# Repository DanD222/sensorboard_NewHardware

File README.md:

# sensorboard_NewHardware
Hardware for a new version of the OpenVario Sensorboard, stemming from discussion in these issues:

https://github.com/Openvario/sensord/issues/23

https://github.com/Openvario/sensord/issues/26

Features / comparison to the original OpenVario sensorboard:

   - Added an ESP32 for polling the sensors and connectivity to the outside world
   - Updated sensors and voltage regulators
   - A USB connector has been added in place of the 6pin I2C connector
   - There are footprints for three differential sensors (DLHR-L30G-E1BD-C-NAV8, 4515DO-DS3BK030DPL, AMS5915)
   - There are two I2C buses:
       - 1 - SDA0/SCL0 is the on-board sensor I2C bus, this goes to the ESP32
       - 2 - SDA1/SCL0 is the external I2C bus, going from the ESP32 to the 10pin IDC connector
       
     Both buses can be linked via solder jumpers on the bottom layer - this allows the sensors to be connected to the IDC connector directly without using the ESP32. This can be useful to get the new sensorboard integrated into the current OpenVario setup without having to implement the ESP32 first.
   - Pins for UART0 and UART1. The UART0 pin header has a 5V pin, so that it can connect for example directly to a HC-05 Bluetooth module (or a board with an RS232 interface)
   - An on-board 12V->5V PSU so that the sensorboard can be used stand-alone
   - Additional filtering - 5VD powers the digital stuff (USB, ESP32 voltage regulator); 5VC powers the sensitive stuff (sensor voltage regulators, audio amp)
   - The audio amp is a class AB TPA6211A1DRBR
   - There are pins around the audio amp so that a daughter board can be used in order to experiment with different amps
   - There are pins for selecting the source to the audio amp. This can be either the ESP32 for future use, or external input (to be backwards-compatible)
   - The OAT sensor has been moved to a 2.5mm jack
   - The audio output is on a 3.5mm stereo jack

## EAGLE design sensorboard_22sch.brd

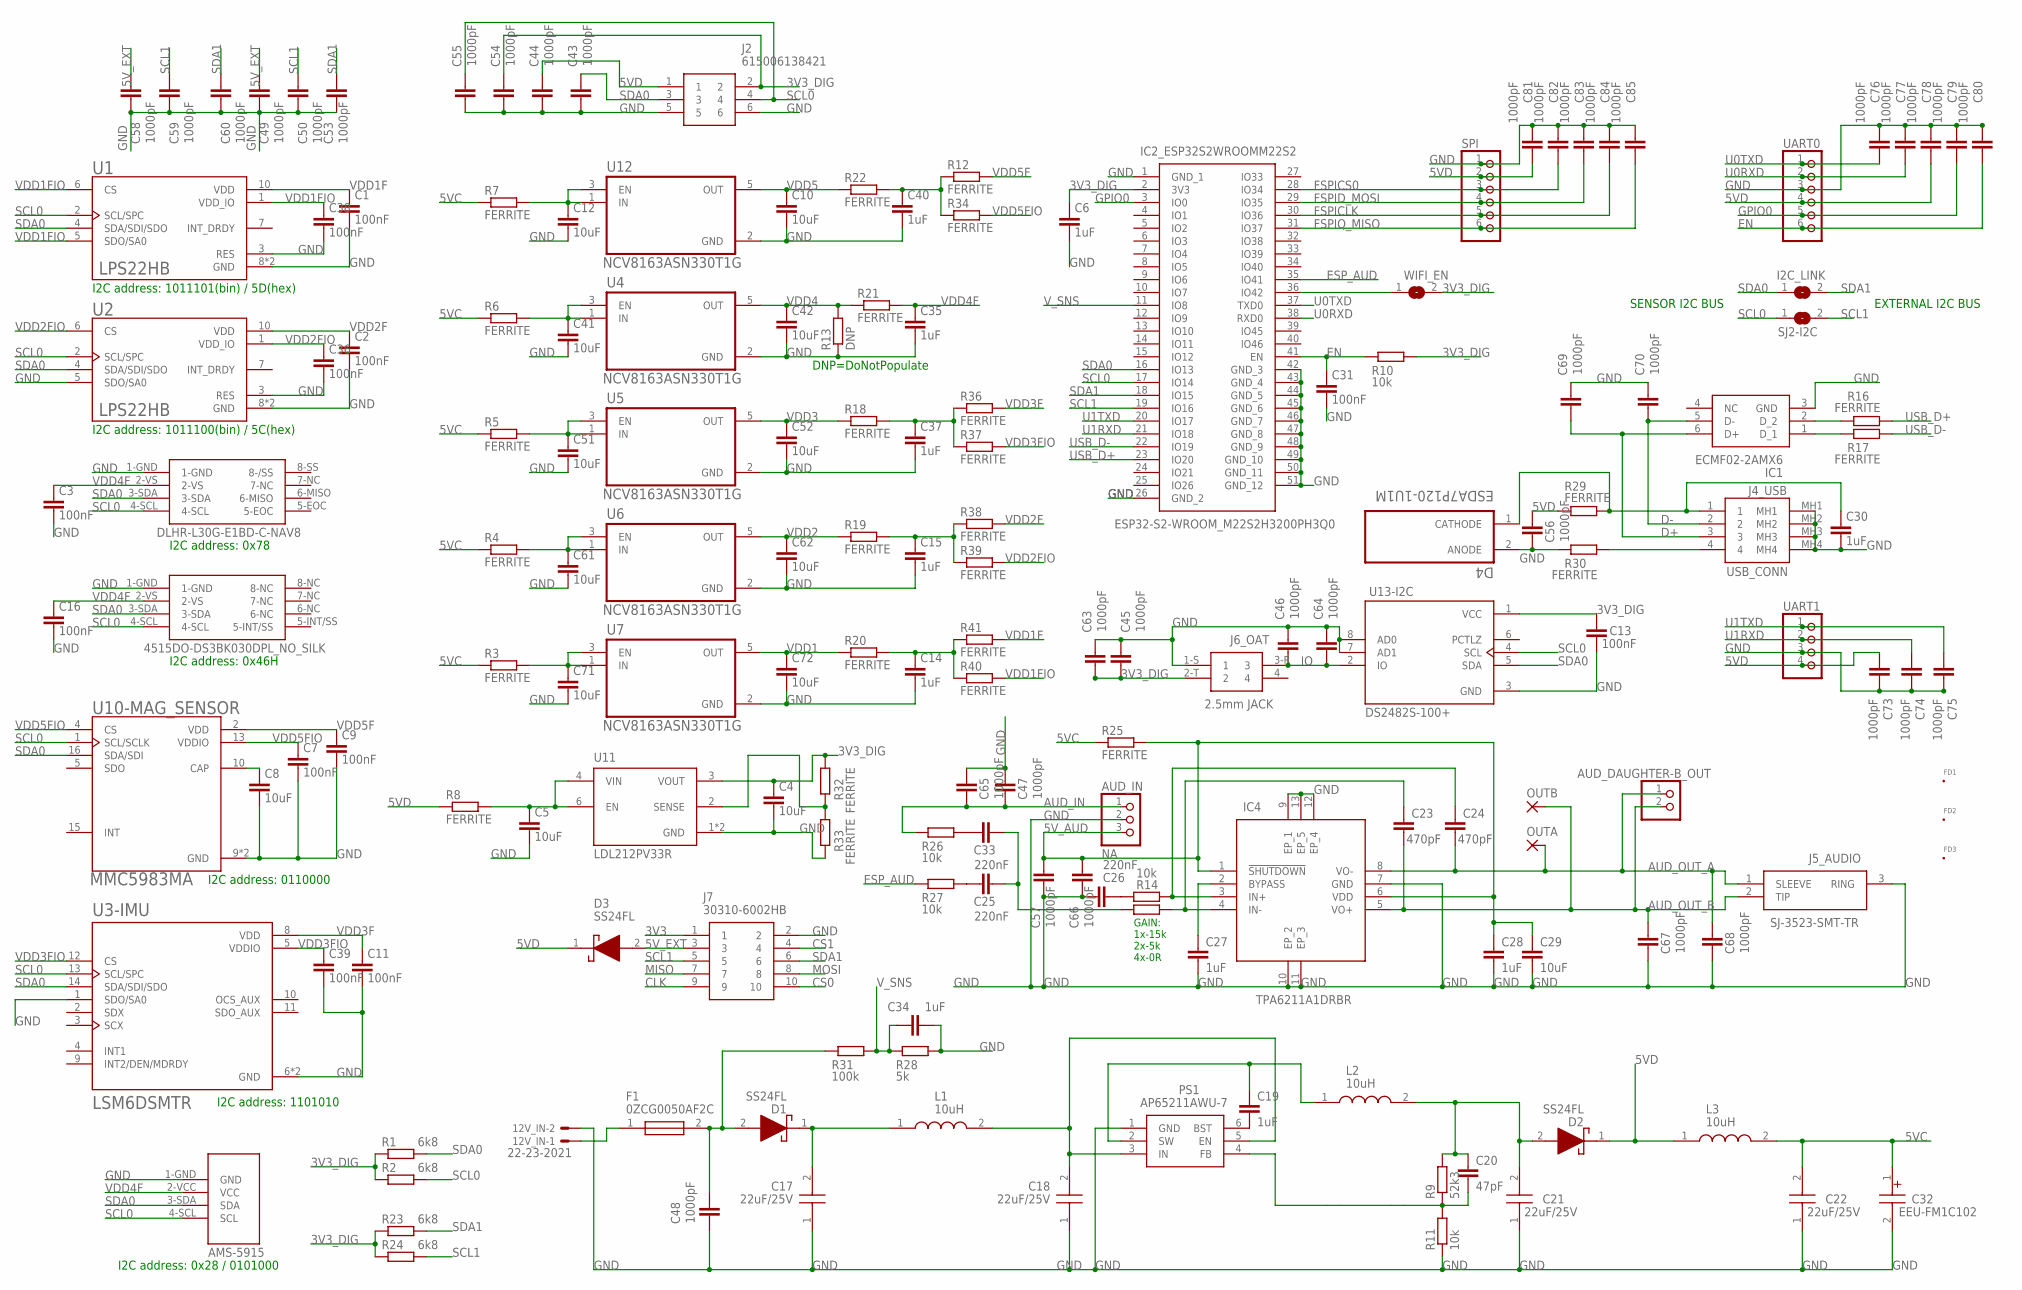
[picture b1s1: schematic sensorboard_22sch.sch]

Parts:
12V_IN: 22-23-2021
AUD_DAUGHTER-B_OUT: PINHD-1X2; 1X02
AUD_IN: NA; 1X03
C1, C2, C3, C7, C9, C11, C13, C16, C31, C36, C38, C39: 100nF; C0402
C4, C5, C8, C10, C12, C29, C41, C42, C51, C52, C61, C62, C71, C72: 10uF; C0805
C6, C14, C15, C19, C27, C28, C30, C34, C35, C37, C40: 1uF; C0603
C17, C18, C21, C22: 22uF/25V; CAPC3216X180N
C20: 47pF; C0402
C23, C24: 470pF; C0805
C25, C26, C33: 220nF; C1206
C32: EEU-FM1C102; CAPPRD500W65D1000H2200
C43, C44, C45, C46, C47, C48, C49, C50, C53, C54, C55, C56, C57, C58, C59, C60, C63, C64, C65, C66, C67, C68, C69, C70, C73, C74, C75, C76, C77, C78, C79, C80, C81, C82, C83, C84, C85: 1000pF; C0402
D1, D2, D3: SS24FL; SODFL3617X108N
D4: ESDA7P120-1U1M; DIO_ESDA13P70-1U1M
DLHR-L30G-E1BD-C-NAV8: DLHR-L30G-E1BD-C-NAV8
F1: 0ZCG0050AF2C; FUSC4632X75N
FD1, FD2, FD3: FID_20MIL_P; FID_020_P
I2C_LINK: SJ
IC1: ECMF02-2AMX6; SON50P150X170X55-6N
IC2_ESP32S2WROOMM22S2: ESP32-S2-WROOM_M22S2H3200PH3Q0; ESP32S2WROOMM22S2H3200PH3Q0
IC4: TPA6211A1DRBR; TPS7A8033DRBT
J2: 615006138421
J4_USB: USB_CONN; 737250110BLF
J5_AUDIO: SJ-3523-SMT-TR; SJ3523SMTTR
J6_OAT: 2.5mm JACK; SJ-2523-SMT-TR
J7: 30310-6002HB; SHDR10W64P254_2X5_2030X878X930
L1, L2, L3: 10uH; FDSD0420WH150MP3
OUTA: SMD2_SMALLSMALL; SMD2_SMALL
OUTB: SMD2_SMALLSMALL; SMD2_SMALL
PS1: AP65211AWU-7; SOT95P280X90-6N
R1, R2, R23, R24: 6k8; R0402
R3, R4, R5, R6, R7, R8, R12, R16, R17, R18, R19, R20, R21, R22, R25, R29, R30, R34, R36, R37, R38, R39, R40, R41: FERRITE; R0805
R9: 52k3; R0402
R10, R11, R14, R26, R27: 10k; R0402
R13: DNP; R0805
R15: R-EU_R0402; R0402
R28: 5k; R0402
R31: 100k; R0402
R32, R33: FERRITE; R0402
SJ2-I2C: SJ
SPI: PINHD-1X6; 1X06
U1, U2: LPS22HB; LGA10R50P2X3_200X200X80
U3-IMU: LSM6DSMTR; PQFN50P300X250X86-14N
U4, U5, U6, U7, U12: NCV8163ASN330T1G; SOP95P275X110-5N
U10-MAG_SENSOR: MMC5983MA; LGA16R50P4X4_330X330X100
U11: LDL212PV33R; SON50P200X200X80-7N
U13-I2C: DS2482S-100+; SOIC127P600X175-8N
U$1: AMS-5915
U$4: 4515DO-DS3BK030DPL_NO_SILKNO_SILK; 4515DO-DS3BK030DPL_NO_SILK
UART0: PINHD-1X6; 1X06
UART1: PINHD-1X4; 1X04
WIFI_EN: SJ

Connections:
3V3: J7.1
3V3_DIG: C4.1, C6.1, C13.1, C45.1, C54.2, C63.1, IC2_ESP32S2WROOMM22S2.2 (3V3), J2.2, J6_OAT.2-T (2), R1.1, R2.1, R10.2, R23.1, R24.1, R32.2, U11.3 (VOUT), U13-I2C.1 (VCC), WIFI_EN.2
5VC: C22.2, C32.1 (+), L3.2, R3.1, R4.1, R5.1, R6.1, R7.1, R25.1
5VD: C44.2, C56.2, C73.1, C78.2, C81.2, D2.1 (K), D3.1 (K), J2.1, L3.1, R8.1, R29.1, SPI.2, UART0.4, UART1.4
5V_AUD: AUD_IN.3, C28.1, C29.1, C57.2, C66.2, IC4.1 (!SHUTDOWN), IC4.6 (VDD), R25.2
5V_EXT: C49.2, C58.2, D3.2 (A), J7.3
AUD_IN: AUD_IN.1, C47.1, C65.1, R26.1
AUD_OUT_A: AUD_DAUGHTER-B_OUT.1, C24.2, C68.2, IC4.8 (VO-), J5_AUDIO.1 (SLEEVE), OUTA.1
AUD_OUT_B: AUD_DAUGHTER-B_OUT.2, C23.2, C67.2, IC4.5 (VO+), J5_AUDIO.2 (TIP), OUTB.1
CLK: J7.9
CS0: J7.10
CS1: J7.4
D+: C69.1, IC1.6 (D+), J4_USB.3
D-: C70.1, IC1.5 (D-), J4_USB.2
EN: C31.1, C80.2, IC2_ESP32S2WROOMM22S2.41 (EN), R10.1, UART0.6
ESP_AUD: IC2_ESP32S2WROOMM22S2.35 (IO41), R27.1
FSPICLK: C84.2, IC2_ESP32S2WROOMM22S2.30 (IO36), SPI.5
FSPICS0: C82.2, IC2_ESP32S2WROOMM22S2.28 (IO34), SPI.3
FSPID_MOSI: C83.2, IC2_ESP32S2WROOMM22S2.29 (IO35), SPI.4
FSPIQ_MISO: C85.2, IC2_ESP32S2WROOMM22S2.31 (IO37), SPI.6
GND: 12V_IN.2, AUD_IN.2, C1.2, C2.2, C3.2, C4.2, C5.2, C6.2, C7.2, C8.2, C9.2, C10.2, C11.2, C12.2, C13.2, C14.2, C15.2, C16.2, C17.1, C18.1, C21.1, C22.1, C26.1, C27.2, C28.2, C29.2, C30.2, C31.2, C32.2 (-), C34.2, C35.2, C36.2, C37.2, C38.2, C39.2, C40.2, C41.2, C42.2, C43.1, C44.1, C45.2, C46.2, C47.2, C48.1, C49.1, C50.1, C51.2, C52.2, C53.1, C54.1, C55.1, C56.1, C57.1, C58.1, C59.1, C60.1, C61.2, C62.2, C63.2, C64.2, C65.2, C66.1, C67.1, C68.1, C69.2, C70.2, C71.2, C72.2, C73.2, C74.2, C75.2, C76.1, C77.1, C78.1, C79.1, C80.1, C81.1, C82.1, C83.1, C84.1, C85.1, D4.2 (ANODE), DLHR-L30G-E1BD-C-NAV8.1-GND, IC1.3 (GND), IC2_ESP32S2WROOMM22S2.1 (GND_1), IC2_ESP32S2WROOMM22S2.26 (GND_2), IC2_ESP32S2WROOMM22S2.42 (GND_3), IC2_ESP32S2WROOMM22S2.43 (GND_4), IC2_ESP32S2WROOMM22S2.44 (GND_5), IC2_ESP32S2WROOMM22S2.45 (GND_6), IC2_ESP32S2WROOMM22S2.46 (GND_7), IC2_ESP32S2WROOMM22S2.47 (GND_8), IC2_ESP32S2WROOMM22S2.48 (GND_9), IC2_ESP32S2WROOMM22S2.49 (GND_10), IC2_ESP32S2WROOMM22S2.50 (GND_11), IC2_ESP32S2WROOMM22S2.51 (GND_12), IC4.7 (GND), IC4.9 (EP_1), IC4.10 (EP_2), IC4.11 (EP_3), IC4.12 (EP_4), IC4.13 (EP_5), J2.5, J2.6, J4_USB.MH1, J4_USB.MH2, J4_USB.MH3, J4_USB.MH4, J5_AUDIO.3 (RING), J6_OAT.1-S (1), J7.2, PS1.1 (GND), R11.1, R13.1, R28.2, R30.1, R33.1, SPI.1, U1.3 (RES), U1.8 (GND), U1.9 (GND), U2.3 (RES), U2.5 (SDO/SA0), U2.8 (GND), U2.9 (GND), U3-IMU.1 (SDO/SA0), U3-IMU.6 (GND), U3-IMU.7 (GND), U4.2 (GND), U5.2 (GND), U6.2 (GND), U7.2 (GND), U10-MAG_SENSOR.9 (GND), U10-MAG_SENSOR.11 (GND), U11.1 (GND), U11.7 (GND), U12.2 (GND), U13-I2C.3 (GND), U13-I2C.7 (AD1), U13-I2C.8 (AD0), U$1.1-GND (GND), U$4.1-GND, UART0.3, UART1.3
GPIO0: C79.2, IC2_ESP32S2WROOMM22S2.3 (IO0), UART0.5
IO: C46.1, C64.1, J6_OAT.3-R (3), U13-I2C.2 (IO)
MISO: J7.7
MOSI: J7.8
unnamed: C8.1, U10-MAG_SENSOR.10 (CAP)
unnamed: C30.1, D4.1 (CATHODE), J4_USB.1, R29.2
unnamed: C23.1, IC4.4 (IN-), R15.2
unnamed: C17.2, D1.1 (K), L1.1
unnamed: C18.2, L1.2, PS1.3 (IN), PS1.5 (EN)
unnamed: C25.2, C33.2, R15.1
unnamed: C20.2, PS1.4 (FB), R9.1, R11.2
unnamed: C19.1, L2.1, PS1.2 (SW)
unnamed: C19.2, PS1.6 (BST)
unnamed: C24.1, IC4.3 (IN+), R14.2
unnamed: C26.2, R14.1
unnamed: J4_USB.4, R30.2
unnamed: 12V_IN.1, F1.1
unnamed: IC2_ESP32S2WROOMM22S2.36 (IO42), WIFI_EN.1
unnamed: C27.1, IC4.2 (BYPASS)
unnamed: IC1.1 (D_1), R17.1
unnamed: IC1.2 (D_2), R16.1
unnamed: C25.1, R27.2
unnamed: C33.1, R26.2
unnamed: C20.1, C21.2, D2.2 (A), L2.2, R9.2
unnamed: C48.2, D1.2 (A), F1.2, R31.1
unnamed: R32.1, R33.2, U11.2 (SENSE)
SCL0: C55.2, DLHR-L30G-E1BD-C-NAV8.4-SCL, IC2_ESP32S2WROOMM22S2.17 (IO14), J2.4, R2.2, SJ2-I2C.1, U1.2 (SCL/SPC), U2.2 (SCL/SPC), U3-IMU.13 (SCL/SPC), U10-MAG_SENSOR.1 (SCL/SCLK), U13-I2C.4 (SCL), U$1.4-SCL (SCL), U$4.4-SCL
SCL1: C50.2, C59.2, IC2_ESP32S2WROOMM22S2.19 (IO16), J7.5, R24.2, SJ2-I2C.2
SDA0: C43.2, DLHR-L30G-E1BD-C-NAV8.3-SDA, I2C_LINK.1, IC2_ESP32S2WROOMM22S2.16 (IO13), J2.3, R1.2, U1.4 (SDA/SDI/SDO), U2.4 (SDA/SDI/SDO), U3-IMU.14 (SDA/SDI/SDO), U10-MAG_SENSOR.16 (SDA/SDI), U13-I2C.5 (SDA), U$1.3-SDA (SDA), U$4.3-SDA
SDA1: C53.2, C60.2, I2C_LINK.2, IC2_ESP32S2WROOMM22S2.18 (IO15), J7.6, R23.2
U0RXD: C77.2, IC2_ESP32S2WROOMM22S2.38 (RXD0), UART0.2
U0TXD: C76.2, IC2_ESP32S2WROOMM22S2.37 (TXD0), UART0.1
U1RXD: C74.1, IC2_ESP32S2WROOMM22S2.21 (IO18), UART1.2
U1TXD: C75.1, IC2_ESP32S2WROOMM22S2.20 (IO17), UART1.1
USB_D+: IC2_ESP32S2WROOMM22S2.23 (IO20), R16.2
USB_D-: IC2_ESP32S2WROOMM22S2.22 (IO19), R17.2
VDD1: C72.1, R20.1, U7.5 (OUT)
VDD1F: C1.1, R41.2, U1.10 (VDD)
VDD1FI: C14.1, R20.2, R40.1, R41.1
VDD1FIO: C38.1, R40.2, U1.1 (VDD_IO), U1.5 (SDO/SA0), U1.6 (CS)
VDD1P: C71.1, R3.2, U7.1 (IN), U7.3 (EN)
VDD2: C62.1, R19.1, U6.5 (OUT)
VDD2F: C2.1, R38.2, U2.10 (VDD)
VDD2FI: C15.1, R19.2, R38.1, R39.1
VDD2FIO: C36.1, R39.2, U2.1 (VDD_IO), U2.6 (CS)
VDD2P: C61.1, R4.2, U6.1 (IN), U6.3 (EN)
VDD3: C52.1, R18.1, U5.5 (OUT)
VDD3F: C11.1, R36.2, U3-IMU.8 (VDD)
VDD3FI: C37.1, R18.2, R36.1, R37.1
VDD3FIO: C39.1, R37.2, U3-IMU.5 (VDDIO), U3-IMU.12 (CS)
VDD3P: C51.1, R5.2, U5.1 (IN), U5.3 (EN)
VDD4: C42.1, R13.2, R21.1, U4.5 (OUT)
VDD4F: C3.1, C16.1, C35.1, DLHR-L30G-E1BD-C-NAV8.2-VS, R21.2, U$1.2-VCC (VCC), U$4.2-VS
VDD4P: C41.1, R6.2, U4.1 (IN), U4.3 (EN)
VDD5: C10.1, R22.1, U12.5 (OUT)
VDD5F: C9.1, R12.2, U10-MAG_SENSOR.2 (VDD)
VDD5FI: C40.1, R12.1, R22.2, R34.1
VDD5FIO: C7.1, R34.2, U10-MAG_SENSOR.4 (CS), U10-MAG_SENSOR.13 (VDDIO)
VDD5P: C12.1, R7.2, U12.1 (IN), U12.3 (EN)
VDD_DIGP: C5.1, R8.2, U11.4 (VIN), U11.6 (EN)
V_SNS: C34.1, IC2_ESP32S2WROOMM22S2.11 (IO8), R28.1, R31.2

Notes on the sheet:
SENSOR I2C BUS
EXTERNAL I2C BUS
GAIN: 1x-15k 2x-5k 4x-0R
I2C address: 1101010
I2C address: 0110000
I2C address: 1011101(bin) / 5D(hex)
I2C address: 1011100(bin) / 5C(hex)
I2C address: 0x78
I2C address: 0x46H
I2C address: 0x28 / 0101000
DNP=DoNotPopulate

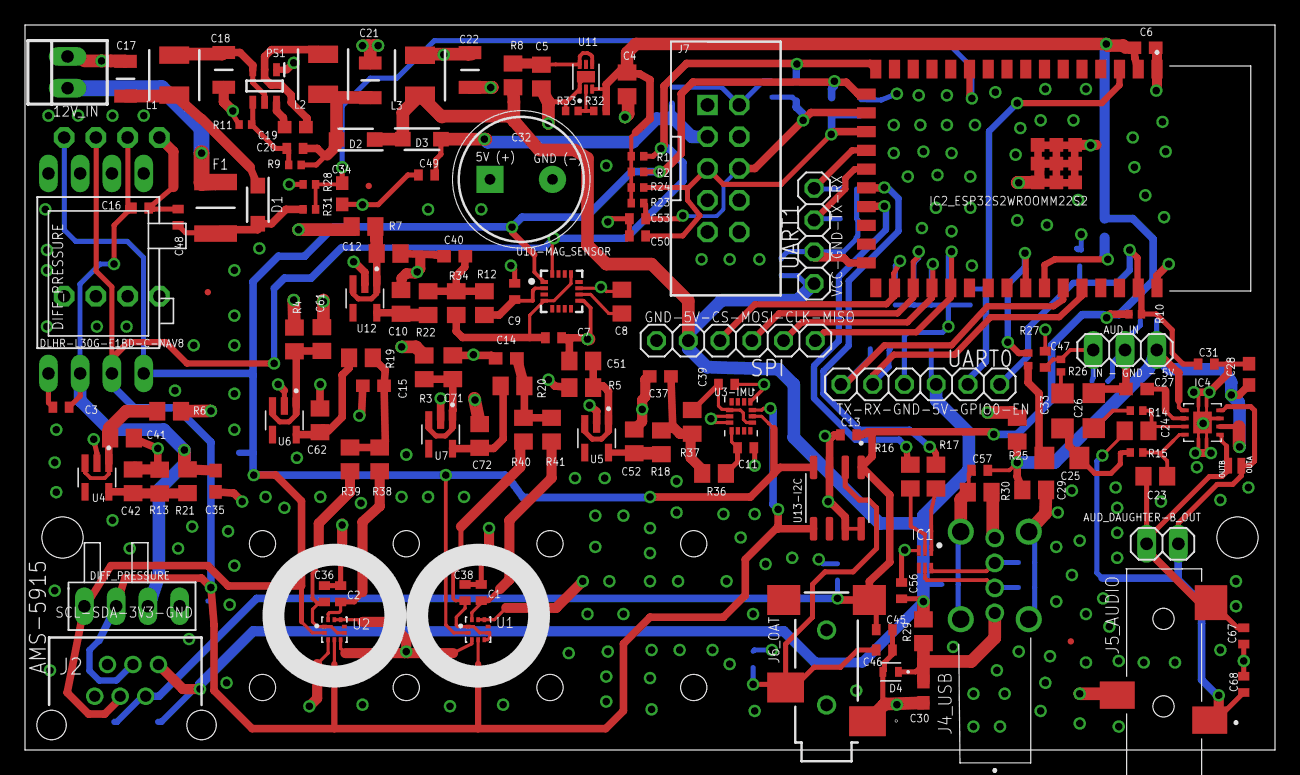
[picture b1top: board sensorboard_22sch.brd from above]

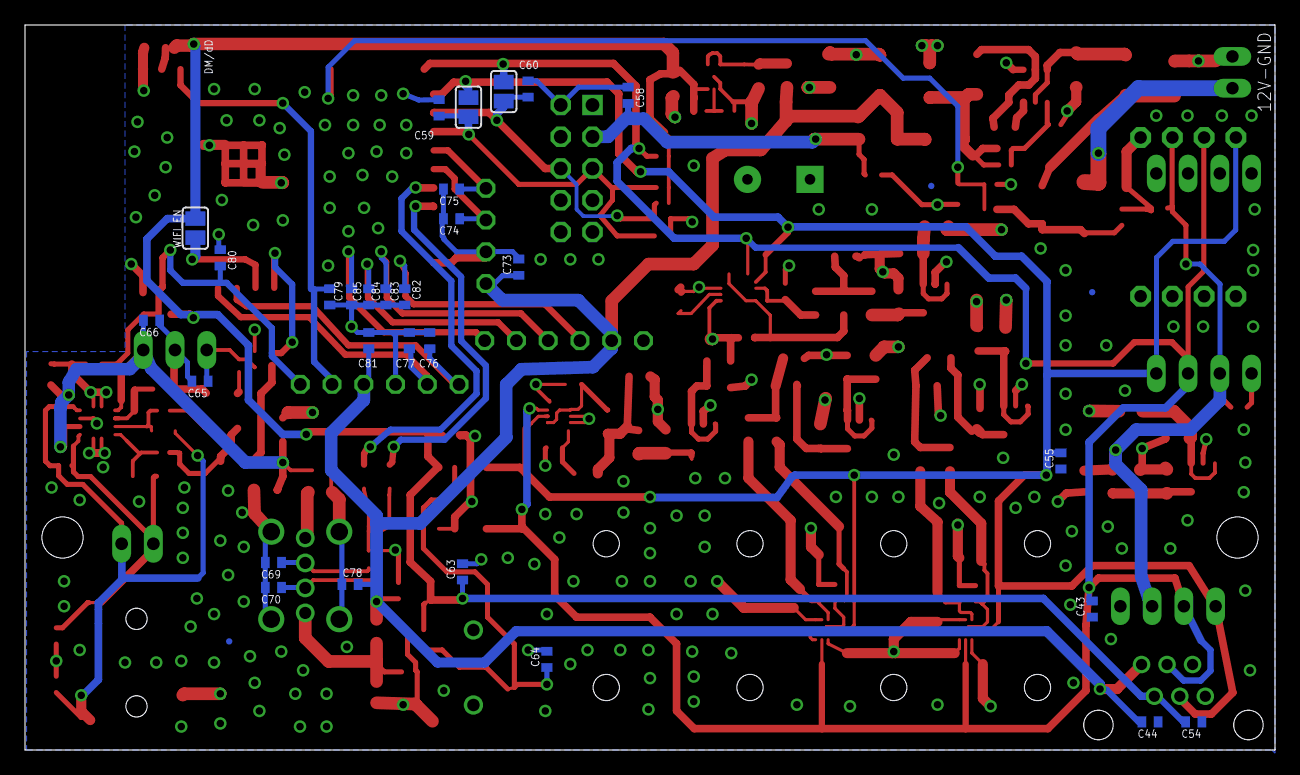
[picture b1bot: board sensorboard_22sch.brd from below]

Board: 4 copper layers, 100.0 x 58.0 mm, 170 parts (29 on the bottom side), 76 nets.

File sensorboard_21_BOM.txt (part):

Partlist exported from /Users/dan/openvario/hpmax/sensorboard_21.sch at 8/3/21 23:23 PM

Part                  Value                          Device                            Package                        Description                                                                                                                                           4515DO-DS3BK030DPL_NO_SILK AMS-5915 ARROW_ELECTRONICS-PURCHASE-URL                              AVAILABILITY DESCRIPTION                                                                                                                   DIGIKEY-PURCHASE-URL                              DLHR-L30G-E1BD-C-NAV8 HEIGHT  MANUFACTURER_NAME         MANUFACTURER_PART_NUMBER        MF                 MOUSER-PURCHASE-URL                              MOUSER_PART_NUMBER   MOUSER_PRICE-STOCK                                                                                                             MP               MPN        OC_FARNELL OC_NEWARK PACKAGE                     POPULARITY PRICE PURCHASE-URL                                                  SPICEPREFIX
12V_IN                22-23-2021                     22-23-2021                        22-23-2021                     .100" (2.54mm) Center Header - 2 Pin                                                                                                                                                                                                                                                                                                                                                                                                                                                                                                       MOLEX                                                                                                                                                                                                                                    22-23-2021 1462926    25C3832                               40                                                                                        
AUD_DAUGHTER-B_OUT                                   PINHD-1X2                         1X02                           PIN HEADER                                                                                                                                                                                                                                                                                                                                                                                                                                                                                                                                                                                                                                                                                                                                                                                                                                      98                                                                                        
AUD_IN                                               PINHD-1X3                         1X03                           PIN HEADER                                                                                                                                                                                                                                                                                                                                                                                                                                                                                                                                                                                                                                                                                                                                                                                                                                      92                                                                                        
C1                    100nF                          C-EUC0603                         C0603                          CAPACITOR, European symbol                                                                                                                                                                                                                                                                                                                                                                                                                                                                                                                                                                                                                                                                                                                                                                                                                      73                                                                             C          
C2                    100nF                          C-EUC0603                         C0603                          CAPACITOR, European symbol                                                                                                                                                                                                                                                                                                                                                                                                                                                                                                                                                                                                                                                                                                                                                                                                                      73                                                                             C          
C3                    100nF                          C-EUC0805                         C0805                          CAPACITOR, European symbol                                                                                                                                                                                                                                                                                                                                                                                                                                                                                                                                                                                                                                                                                                                                                                                                                      88                                                                             C          
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
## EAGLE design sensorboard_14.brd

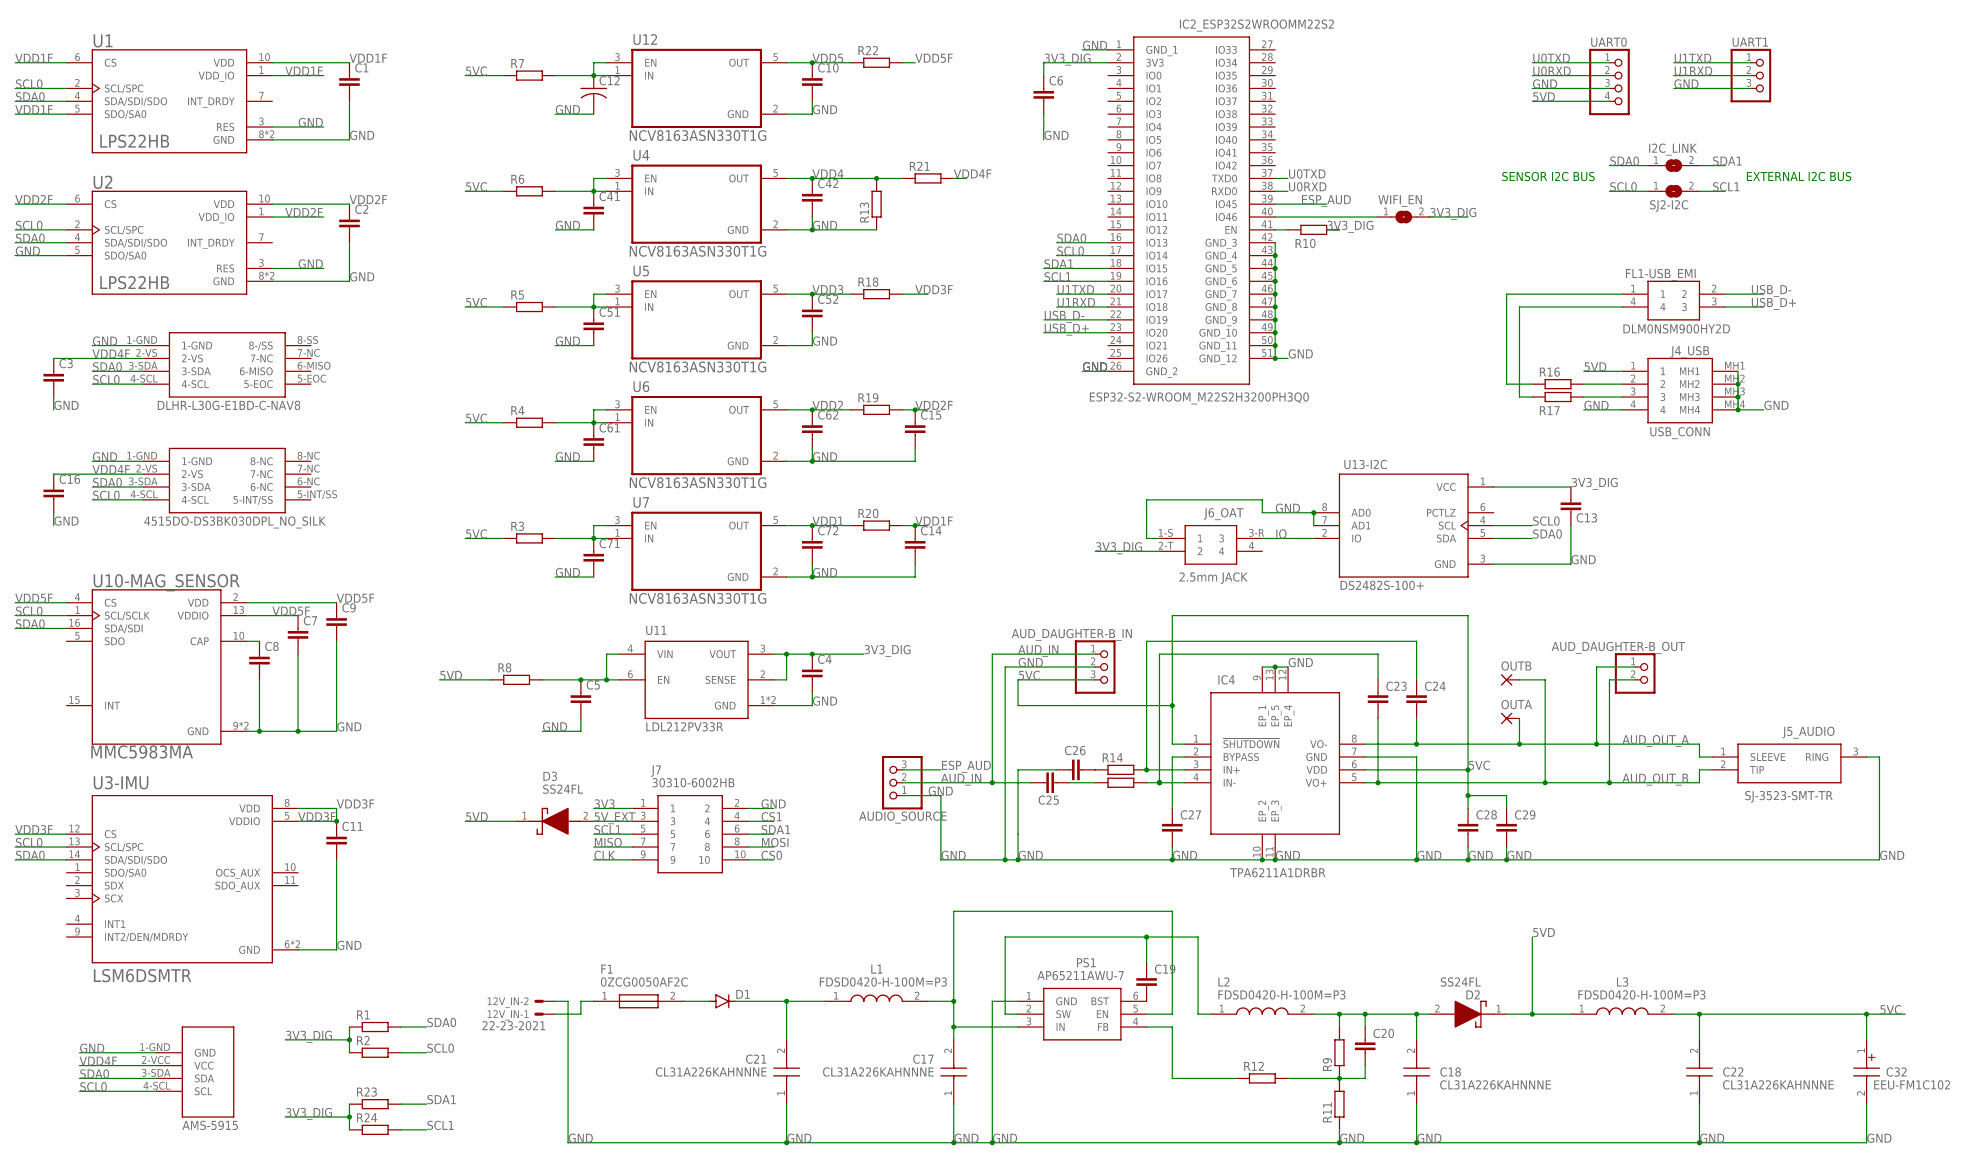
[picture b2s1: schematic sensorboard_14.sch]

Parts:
12V_IN: 22-23-2021
AUDIO_SOURCE: PINHD-1X3; 1X03
AUD_DAUGHTER-B_IN: PINHD-1X3; 1X03
AUD_DAUGHTER-B_OUT: PINHD-1X2; 1X02
C1, C2: C-EUC0603; C0603
C3, C4, C5, C6, C7, C8, C9, C10, C11, C13, C14, C15, C16, C19, C20, C23, C24, C41, C42, C51, C52, C61, C62, C71, C72: C-EUC0805; C0805
C12: C-USC0805; C0805
C17, C18, C21, C22: CL31A226KAHNNNE; CAPC3216X180N
C25, C26, C27, C28, C29: C-EUC1206; C1206
C32: EEU-FM1C102; CAPPRD500W65D1000H2200
D1: DIODE-DO-214AC; DO-214AC
D2, D3: SS24FL; SODFL3617X108N
DLHR-L30G-E1BD-C-NAV8: DLHR-L30G-E1BD-C-NAV8
F1: 0ZCG0050AF2C; FUSC4632X75N
FL1-USB_EMI: DLM0NSM900HY2D; DLM0NSB120HY2B
I2C_LINK: SJ
IC2_ESP32S2WROOMM22S2: ESP32-S2-WROOM_M22S2H3200PH3Q0; ESP32S2WROOMM22S2H3200PH3Q0
IC4: TPA6211A1DRBR; TPS7A8033DRBT
J4_USB: USB_CONN; 737250110BLF
J5_AUDIO: SJ-3523-SMT-TR; SJ3523SMTTR
J6_OAT: 2.5mm JACK; SJ-2523-SMT-TR
J7: 30310-6002HB; SHDR10W64P254_2X5_2030X878X930
L1, L2, L3: FDSD0420-H-100M=P3; FDSD0420WH150MP3
OUTA: SMD2_SMALLSMALL; SMD2_SMALL
OUTB: SMD2_SMALLSMALL; SMD2_SMALL
PS1: AP65211AWU-7; SOT95P280X90-6N
R1, R2, R3, R4, R5, R6, R7, R8, R9, R10, R11, R12, R13, R14, R15, R16, R17, R18, R19, R20, R21, R22, R23, R24: R-EU_R0805; R0805
SJ2-I2C: SJ
U1, U2: LPS22HB; LGA10R50P2X3_200X200X80
U3-IMU: LSM6DSMTR; PQFN50P300X250X86-14N
U4, U5, U6, U7, U12: NCV8163ASN330T1G; SOP95P275X110-5N
U10-MAG_SENSOR: MMC5983MA; LGA16R50P4X4_330X330X100
U11: LDL212PV33R; SON50P200X200X80-7N
U13-I2C: DS2482S-100+; SOIC127P600X175-8N
U$1: AMS-5915
U$4: 4515DO-DS3BK030DPL_NO_SILKNO_SILK; 4515DO-DS3BK030DPL_NO_SILK
UART0: PINHD-1X4; 1X04
UART1: PINHD-1X3; 1X03
WIFI_EN: SJ

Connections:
3V3: J7.1
3V3_DIG: C4.1, C6.1, C13.1, IC2_ESP32S2WROOMM22S2.2 (3V3), J6_OAT.2-T (2), R1.1, R2.1, R10.2, R23.1, R24.1, U11.2 (SENSE), U11.3 (VOUT), U13-I2C.1 (VCC), WIFI_EN.2
5VC: AUD_DAUGHTER-B_IN.3, C22.2, C28.1, C29.1, C32.1 (+), IC4.1 (!SHUTDOWN), IC4.6 (VDD), L3.2, R3.1, R4.1, R5.1, R6.1, R7.1
5VD: D2.1 (K), D3.1 (K), J4_USB.1, L3.1, R8.1, UART0.4
5V_EXT: D3.2 (A), J7.3
AUD_IN: AUDIO_SOURCE.2, AUD_DAUGHTER-B_IN.1, C25.1
AUD_OUT_A: AUD_DAUGHTER-B_OUT.1, C24.2, IC4.8 (VO-), J5_AUDIO.1 (SLEEVE), OUTA.1
AUD_OUT_B: AUD_DAUGHTER-B_OUT.2, C23.2, IC4.5 (VO+), J5_AUDIO.2 (TIP), OUTB.1
CLK: J7.9
CS0: J7.10
CS1: J7.4
ESP_AUD: AUDIO_SOURCE.3, IC2_ESP32S2WROOMM22S2.39 (IO45)
GND: 12V_IN.2, AUDIO_SOURCE.1, AUD_DAUGHTER-B_IN.2, C1.2, C2.2, C3.2, C4.2, C5.2, C6.2, C7.2, C8.2, C9.2, C10.2, C11.2, C12.2, C13.2, C14.2, C15.2, C16.2, C17.1, C18.1, C21.1, C22.1, C26.1, C27.2, C28.2, C29.2, C32.2 (-), C41.2, C42.2, C51.2, C52.2, C61.2, C62.2, C71.2, C72.2, DLHR-L30G-E1BD-C-NAV8.1-GND, IC2_ESP32S2WROOMM22S2.1 (GND_1), IC2_ESP32S2WROOMM22S2.26 (GND_2), IC2_ESP32S2WROOMM22S2.42 (GND_3), IC2_ESP32S2WROOMM22S2.43 (GND_4), IC2_ESP32S2WROOMM22S2.44 (GND_5), IC2_ESP32S2WROOMM22S2.45 (GND_6), IC2_ESP32S2WROOMM22S2.46 (GND_7), IC2_ESP32S2WROOMM22S2.47 (GND_8), IC2_ESP32S2WROOMM22S2.48 (GND_9), IC2_ESP32S2WROOMM22S2.49 (GND_10), IC2_ESP32S2WROOMM22S2.50 (GND_11), IC2_ESP32S2WROOMM22S2.51 (GND_12), IC4.7 (GND), IC4.9 (EP_1), IC4.10 (EP_2), IC4.11 (EP_3), IC4.12 (EP_4), IC4.13 (EP_5), J4_USB.4, J4_USB.MH1, J4_USB.MH2, J4_USB.MH3, J4_USB.MH4, J5_AUDIO.3 (RING), J6_OAT.1-S (1), J7.2, PS1.1 (GND), R11.1, R13.1, U1.3 (RES), U1.8 (GND), U1.9 (GND), U2.3 (RES), U2.5 (SDO/SA0), U2.8 (GND), U2.9 (GND), U3-IMU.6 (GND), U3-IMU.7 (GND), U4.2 (GND), U5.2 (GND), U6.2 (GND), U7.2 (GND), U10-MAG_SENSOR.9 (GND), U10-MAG_SENSOR.11 (GND), U11.1 (GND), U11.7 (GND), U12.2 (GND), U13-I2C.3 (GND), U13-I2C.7 (AD1), U13-I2C.8 (AD0), U$1.1-GND (GND), U$4.1-GND, UART0.3, UART1.3
IO: J6_OAT.3-R (3), U13-I2C.2 (IO)
MISO: J7.7
MOSI: J7.8
unnamed: C8.1, U10-MAG_SENSOR.10 (CAP)
unnamed: IC2_ESP32S2WROOMM22S2.41 (EN), R10.1
unnamed: C23.1, IC4.4 (IN-), R15.2
unnamed: C21.2, D1.C, L1.1
unnamed: C17.2, L1.2, PS1.3 (IN), PS1.5 (EN)
unnamed: C18.2, C20.1, D2.2 (A), L2.2, R9.2
unnamed: C20.2, R9.1, R11.2, R12.2
unnamed: C19.1, L2.1, PS1.2 (SW)
unnamed: PS1.4 (FB), R12.1
unnamed: C19.2, PS1.6 (BST)
unnamed: C24.1, IC4.3 (IN+), R14.2
unnamed: C26.2, R14.1
unnamed: C25.2, R15.1
unnamed: 12V_IN.1, F1.1
unnamed: IC2_ESP32S2WROOMM22S2.40 (IO46), WIFI_EN.1
unnamed: C27.1, IC4.2 (BYPASS)
unnamed: FL1-USB_EMI.1, R16.1
unnamed: FL1-USB_EMI.4, R17.1
unnamed: J4_USB.2, R16.2
unnamed: J4_USB.3, R17.2
unnamed: D1.A, F1.2
SCL0: DLHR-L30G-E1BD-C-NAV8.4-SCL, IC2_ESP32S2WROOMM22S2.17 (IO14), R2.2, SJ2-I2C.1, U1.2 (SCL/SPC), U2.2 (SCL/SPC), U3-IMU.13 (SCL/SPC), U10-MAG_SENSOR.1 (SCL/SCLK), U13-I2C.4 (SCL), U$1.4-SCL (SCL), U$4.4-SCL
SCL1: IC2_ESP32S2WROOMM22S2.19 (IO16), J7.5, R24.2, SJ2-I2C.2
SDA0: DLHR-L30G-E1BD-C-NAV8.3-SDA, I2C_LINK.1, IC2_ESP32S2WROOMM22S2.16 (IO13), R1.2, U1.4 (SDA/SDI/SDO), U2.4 (SDA/SDI/SDO), U3-IMU.14 (SDA/SDI/SDO), U10-MAG_SENSOR.16 (SDA/SDI), U13-I2C.5 (SDA), U$1.3-SDA (SDA), U$4.3-SDA
SDA1: I2C_LINK.2, IC2_ESP32S2WROOMM22S2.18 (IO15), J7.6, R23.2
U0RXD: IC2_ESP32S2WROOMM22S2.38 (RXD0), UART0.2
U0TXD: IC2_ESP32S2WROOMM22S2.37 (TXD0), UART0.1
U1RXD: IC2_ESP32S2WROOMM22S2.21 (IO18), UART1.2
U1TXD: IC2_ESP32S2WROOMM22S2.20 (IO17), UART1.1
USB_D+: FL1-USB_EMI.3, IC2_ESP32S2WROOMM22S2.23 (IO20)
USB_D-: FL1-USB_EMI.2, IC2_ESP32S2WROOMM22S2.22 (IO19)
VDD1: C72.1, R20.1, U7.5 (OUT)
VDD1F: C1.1, C14.1, R20.2, U1.1 (VDD_IO), U1.5 (SDO/SA0), U1.6 (CS), U1.10 (VDD)
VDD1P: C71.1, R3.2, U7.1 (IN), U7.3 (EN)
VDD2: C62.1, R19.1, U6.5 (OUT)
VDD2F: C2.1, C15.1, R19.2, U2.1 (VDD_IO), U2.6 (CS), U2.10 (VDD)
VDD2P: C61.1, R4.2, U6.1 (IN), U6.3 (EN)
VDD3: C52.1, R18.1, U5.5 (OUT)
VDD3F: C11.1, R18.2, U3-IMU.5 (VDDIO), U3-IMU.8 (VDD), U3-IMU.12 (CS)
VDD3P: C51.1, R5.2, U5.1 (IN), U5.3 (EN)
VDD4: C42.1, R13.2, R21.1, U4.5 (OUT)
VDD4F: C3.1, C16.1, DLHR-L30G-E1BD-C-NAV8.2-VS, R21.2, U$1.2-VCC (VCC), U$4.2-VS
VDD4P: C41.1, R6.2, U4.1 (IN), U4.3 (EN)
VDD5: C10.1, R22.1, U12.5 (OUT)
VDD5F: C7.1, C9.1, R22.2, U10-MAG_SENSOR.2 (VDD), U10-MAG_SENSOR.4 (CS), U10-MAG_SENSOR.13 (VDDIO)
VDD5P: C12.1, R7.2, U12.1 (IN), U12.3 (EN)
VDD_DIGP: C5.1, R8.2, U11.4 (VIN), U11.6 (EN)

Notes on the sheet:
SENSOR I2C BUS
EXTERNAL I2C BUS

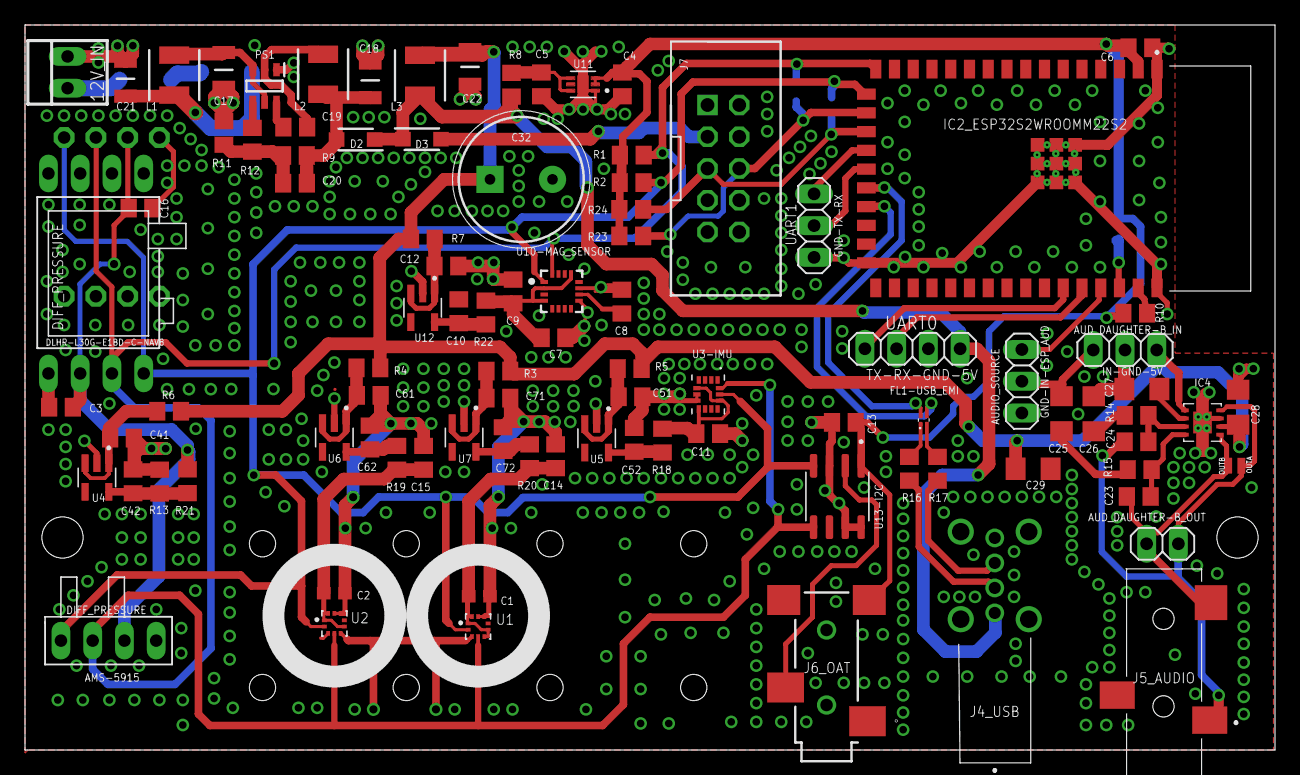
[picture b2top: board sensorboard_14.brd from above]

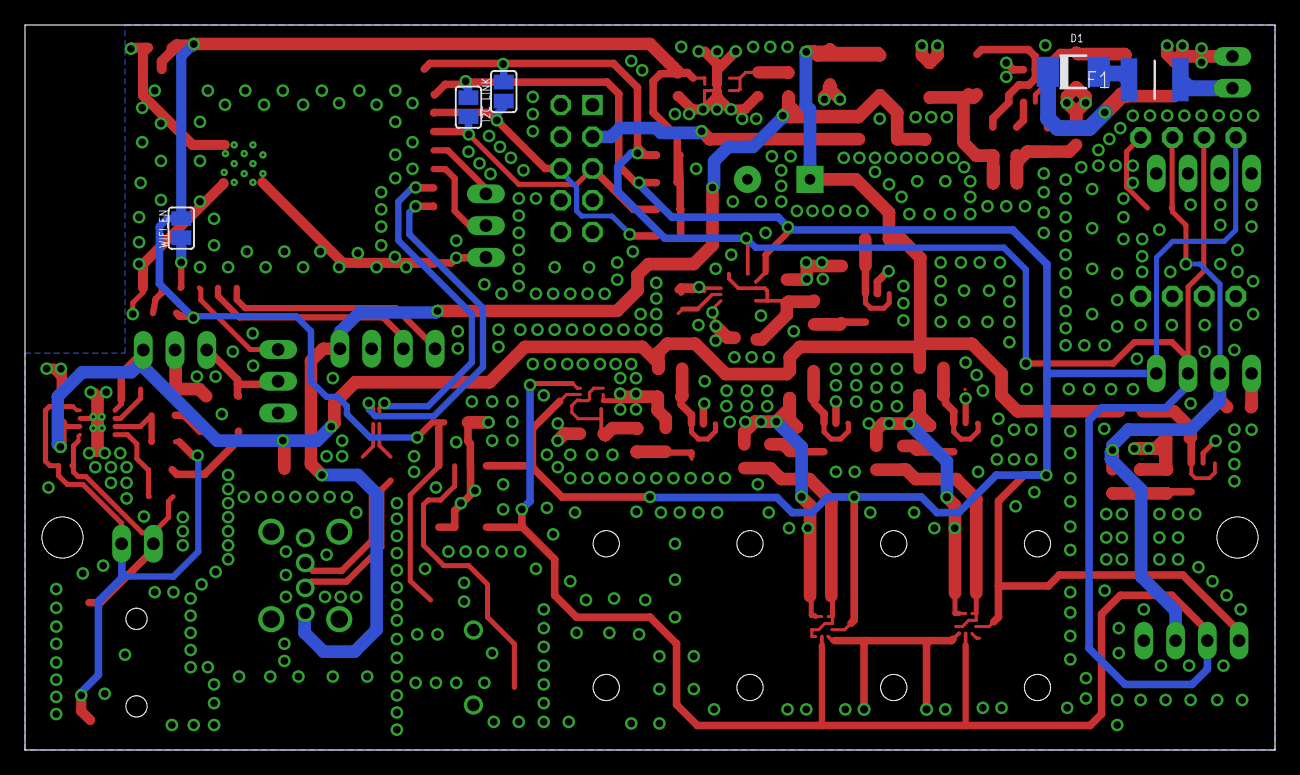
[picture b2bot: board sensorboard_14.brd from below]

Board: 2 copper layers, 100.0 x 58.0 mm, 102 parts (5 on the bottom side), 57 nets.

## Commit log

2020-11-25 upload v14 files
2021-01-23 upload v18 files
2021-02-26 Upload sensorboard_18_DS2_dD2 files
    - Enlarged via drill size
    - Added ESP_AUD pinhead
    Remove sensorboard_18_DS2_dD1 files
2021-02-26 Upload sensorboard_19 files
    Increase via drill size
    Change USB common mode filter to larger part
    Add 6 pin header for SPI, 5V, GND
    Add ESP32 EN pin bypass capacitor
    Remove sensorboard_18 files
2021-02-26 Upload sensorboard_18_DS2_dD2b files
    Add ESP32 EN pin bypass capacitor
    Remove sensorboard_18_DS2_dD2 files
2021-02-28 Upload v20 files
    Extend UART0 connector with EN, GPIO0 pins (Fixes #2)
    Move ESP_AUD, WIFI_EN to different ESP32 pins (Fixes #3)
2021-02-28 Archive v18 files
    Create archive directory with v18 files for use as assembly reference for previous board revision
2021-03-07 Update v20 files
    Add files in Eagle 7 format
2021-03-11 Upload v21 files
    Add resistor divider to 12V input for battery voltage measurement on ESP32
    Extend UART0 connector with VCC pin for HC-05 compatibility
    Add capacitor to summing resistors
    Add capacitor to V_SNS pin
2021-03-16 Upload v21 files
    Added resistor divider to 12V input for battery voltage measurement on ESP32
    Added bypass capacitor to V_SNS resistor
    Extend UART1 connector with VCC pin for HC-05 compatibility
    Modify audio amplifier input summing (resistor + cap on each input)
    Add ferrites to USB power and GND rails
    Add 1uF capacitor to VDD4F rail
2021-11-13 Upload v22 files
    Switched to 4 layer layout
    Added SPI header
    Added optional I2C socket next to AMS-5915
    Added 1000pF capacitors to GND on interface pins to improve RF immunity
    I2C bus resistors changed to 6k8
    All 100nF caps are now 0402, all 1uF caps are 0603, all 10uF caps are 0805. 470pF caps are 0805. 220nF are 1206. 47pF cap is 0402. All resistors are 0402.
